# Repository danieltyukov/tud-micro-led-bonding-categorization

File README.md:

# Micro-LED Bonding Categorization

**A PCB test vehicle, a cleanroom bonding campaign, and an electrical characterization of eight micro-LED assembly conditions.**

TU Delft ECTM + ITEC B.V., February to August 2026. Course project (ET4277 + ET4391) and research contribution, supervised by M. Mastrangeli, H. van Zeijl and A. Abdelwahab, with R. van Hoorn and H. Kuipers (ITEC B.V. / Nexperia). Financed by ITEC B.V. and co-financed by RVO. Extends the v1 board published at [ECTC 2025](https://doi.org/10.1109/ECTC51687.2025.00363).

The question behind the work: when a ~1 mm² LED die is attached to a PCB without mounting pressure (pick-and-release / air-drop), how good is the resulting bond, and what instrument does it take to tell one bonding process from another?

---

## Headline result

**Yield and failure mode separate the eight assembly conditions. Series resistance cannot, and the reason is measured rather than assumed.**

| Condition | Channel yield | Failure modes | Assessment |
|---|---:|---|---|
| 1 | 83.3 % | 1 open, 3 detached | under-bonded |
| 2 | 58.3 % | 4 open, 6 detached | under-bonded |
| 3 | 25.0 % | 4 short, 2 open, 2 cross-lit, 1 suspect | over-bonded, 1 shunt confirmed |
| 4 | 66.7 % | 1 short, 1 open, 1 cross-lit, 1 suspect | over-bonded |
| 5 | **100 %** | none | in window |
| 6 | 75.0 % | 3 detached | under-bonded |
| 7 | **100 %** | none | in window |
| 8 | 83.3 % | 2 short | over-bonded, survivors clean |

A χ² test on the yield and failure-mode distribution gives p = 2.2 × 10⁻⁴. Conditions 5 and 7 lost nothing across every channel.

Series resistance does not discriminate: one-way ANOVA over the seven samples with n ≥ 3 gives F(6,21) = 1.96, not significant. Re-seating the same two jumpers on an unchanged channel moves R_s by **0.84 Ω**, which is 85 % of the apparent die-to-die spread, while the bond resistances being chased are **10 to 100 mΩ**. The experiment was never capable of resolving them, and the repeatability study is what proves it.

<table>
<tr>
<td width="50%"></td>
<td width="50%"></td>
</tr>
<tr>
<td>Yield and failure mode per condition, with Wilson intervals.</td>
<td>Defect map: every die position, every condition.</td>
</tr>
</table>

---

## The three parts of the work

### 1. Board design

A single 93 × 93 mm two-layer FR-4 board (ENIG, all pads gold) carrying every structure needed to characterize a bond on one substrate, so that one cleanroom session yields bond resistance, contact resistivity, sheet resistance and junction thermometry from the same hardware:

- **6 × 6 bond-pad design of experiments** at 3.5 mm pitch: three pad geometries (plain, four corner mini-pads, rounded + mini) crossed with three fillet radii (50 / 100 / 200 µm).
- **TLM ladders** at W = 0.25 / 0.5 / 1.0 mm with spacings 200 to 4000 µm, and **van der Pauw cloverleaves** at W = 1.0 / 0.5 / 0.25 / 0.15 mm.
- **26 Würth WL-SFCC 0404 RGB LEDs**: eight individually addressable, eighteen in 6- and 12-die daisy chains.
- **Four 0402 NTCs** for V_F-based junction thermometry, and an **LCR calibration set** (open / short / 100 Ω 0.1 %).
- Two 32-pin headers breaking every active net out to a breadboard.

Designed in KiCad 9, DRC-clean with full schematic parity, exported fab-ready to the Eurocircuits standard pool. The five SMT parts are reflowed by the fab; the 26 LED bond pads ship as bare gold, because the joint itself is the research subject and has to form under controlled conditions.

Sources, Python generators and the full fab package (gerbers, BOM, CPL, STEP, PDFs) are in [`new-pcb/`](new-pcb/). Report: [`part1/`](part1/ET4277_ET4391_DanielTyukov_5714699_part1_microLED_PCB_electrical_characterization.pdf).

### 2. Cleanroom bonding

Solder paste printed by hand through a 100 µm stencil, dies placed with a Tresky T-3000-PRO die bonder, joint formed on a hot plate with Sn42/Bi57.6/Ag0.4 (T_melt = 138 °C). When the paste melts, surface tension pulls each die toward the centre of its pad set. The same forces can tilt a die and lock it in a crooked position that never recovers, because tilt is the one non-restoring self-alignment mode for a rectangular chip.

<table>
<tr>
<td width="50%"></td>
<td width="50%"></td>
</tr>
<tr>
<td>Board fixtured in the Tresky T-3000-PRO.</td>
<td>Printed bond-pad array before placement.</td>
</tr>
</table>

The analytical contribution is reading the observed self-alignment and tilt against the capillary self-alignment literature to identify which process variable dominates. It is **solder volume**: manual stencil printing gives no volume metering, and volume is exactly the quantity the literature ties most strongly to both placement accuracy and the non-restoring tilt mode.

Report: [`part2/`](part2/ET4277_ET4391_DanielTyukov_5714699_part2_microLED_bonding_self_alignment_die_tilt.pdf). Session photos in [`part2/photos-during-lab2/`](part2/photos-during-lab2/), references in [`part2/downloaded_references/`](part2/downloaded_references/).

### 3. Electrical characterization

Eight blind-coded assembly conditions across five coupons, 40 dice bonded, 4 detached in handling, 36 measurable, 120 individual-die channels. Run as two rounds so that a cheap screen filtered the expensive one.

**Round 1, DMM screen.** Every channel screened for opens, shorts, cross-lighting and detachment with a handheld meter. It called six channels bad; the sweep rig later agreed on all six and disagreed on none in 89 sweeps.

**Round 2, current sweep.** An Arduino UNO rig switching a six-resistor bank (220 Ω to 10 kΩ) against a 100 Ω sense resistor, 63 current levels per sweep, fitting V = V₀ + n·V_T·ln(I) + I·R_s to each channel. 89 channel sweeps plus 9 re-seating repeatability runs.

<table>
<tr>
<td width="50%"></td>
<td width="50%"></td>
</tr>
<tr>
<td>Red, green and blue junctions of one die.</td>
<td>The defect only a current sweep could see.</td>
</tr>
</table>

Three findings about the measurement itself carried more weight than the bond numbers:

- **The ideality factor is a free defect detector.** Any channel fitting outside n = 1.2 to 2.4 has something in parallel with the junction, however normal its curve looks at working current. It caught a ~2.9 kΩ shunt on a contaminated die that the DMM passed at 1.781 V.
- **Green and blue are not fittable at 5 V.** With V_F near 2.8 V the rail leaves only a 20× current range, so V₀, n and R_s trade off and green fits at an unphysical n = 3.2 to 4.0. Red gets 30× and fits cleanly at n = 1.60 to 2.06. Red only.
- **Four instrument defects were found and fixed mid-campaign**, including a hardcoded oversampling shift that would have rescaled every voltage, a 14.4 mV common ADC offset worth 26 % current error at the bottom of the sweep, and an integer-truncated bandgap reference putting a 2 to 3 mV floor on every reading.

Full working log with per-channel results: [`RESULTS/R2_REPORT.md`](RESULTS/R2_REPORT.md). Packaged deliverable with figures, MATLAB and raw data: [`deliverable/`](deliverable/microLED_electrical_characterization/).

**Dummy-die daisy chains (separate experiment, v1 board).** Measured by A. Abdelwahab on the v1 PCB in its own session, six Au-coated 1 mm² dummy dies per chain, one chain per condition. It resolves bond resistance where the LED coupons could not: 0.22 Ω on condition 5 against 0.61 Ω on condition 4, roughly 30 mΩ per joint, with a reported deviation of 11 to 20 mΩ. Its ranking agrees with the LED yield ranking at ρ = −0.92 (p = 0.003). That is agreement between assembly conditions across two different test vehicles and two campaigns, not two structures on one coupon, and it assumes the condition numbering matches. The v2 board carries daisy chains as well, but none were measured: a layout fault left them dead, so they were diagnosed and excluded rather than characterized (see Known limits). Data and figure: [`RESULTS/daisy_chain/`](RESULTS/daisy_chain/).

---

## Known limits

Stated up front, because they decide what these numbers can be used for.

| Limit | Consequence |
|---|---|
| Both voltage taps sit on the breadboard, not on the Tier-1 probe pads | Two female-male jumpers fall inside the measured loop. R_s is not usable for comparing bonds in this build. Kelvin sensing at the probe pads fixes it. |
| 5 V supply | Green and blue fits are unphysical. Red only. |
| Reverse bias measured through the meter's own 10 MΩ input impedance | Detects shunts below ~10 MΩ, cannot grade healthy dies. It confirmed the yield ranking rather than adding to it. |
| Daisy chains read open on every coupon | Layout fault, not a bonding failure: the dice sit rotated 90°, so the chain joins each die's red cathode to its blue cathode and leaves the anode floating. Fixed in the next revision. |
| One coupon carries uncleanable solder smear | Its readings characterize a post-process contamination failure and are excluded from V_F statistics. |
| No NTC readings collected | Ambient drift cannot be separated from self-heating at analysis time. |
| TLM, van der Pauw and impedance spectroscopy | Designed into the board, but the instruments were not available during the campaign. The structures are there for whoever has them. |

---

## Repository layout

| Path | Contents |
|---|---|
| [`new-pcb/`](new-pcb/) | v4 KiCad project, Python generators, Eurocircuits fab package, design notes |
| [`part1/`](part1/) | Board design and characterization-methodology report, project archive, fab quote |
| [`part2/`](part2/) | Bonding process report, cleanroom photos, self-alignment literature |
| [`FINAL_MEASUREMENTS/`](FINAL_MEASUREMENTS/) | Bench procedures, Arduino rig build drawings, MATLAB analysis, figures |
| [`RESULTS/`](RESULTS/) | Raw round 1 and round 2 data, per-channel results, round 2 report |
| [`measurements/`](measurements/) | Measurement plan, equipment limits, sample inventory, decision log |
| [`deliverable/`](deliverable/) | Self-contained characterization package: report, figures, code, data |
| [`old-pcb/`](old-pcb/) | v1 board (ECTC 2025), kept for reference |
| [`docs/`](docs/) | Datasheets, published papers, patent, collaboration notes |
| [`PROJECT_DETAILS.md`](PROJECT_DETAILS.md) | Full project context, v1 board teardown, literature notes |

## Reproducing the analysis

```
cd deliverable/microLED_electrical_characterization/matlab
matlab -batch figures
```

Reads `../data/`, refits every sweep, writes all eight figures, and prints every number quoted in the report. MATLAB R2025b with the Statistics and Machine Learning Toolbox (`anova1`, `chi2cdf`).

Board previews and fab outputs regenerate from `new-pcb/tools/`; see [`new-pcb/README.md`](new-pcb/README.md) and [`new-pcb/FABRICATION_ORDER.md`](new-pcb/FABRICATION_ORDER.md) for the ordering workflow.

## Reports

| Report | File |
|---|---|
| Part 1: A PCB Test Board for Electrical Characterization of Solder-Bonded Micro-LEDs | [PDF](part1/ET4277_ET4391_DanielTyukov_5714699_part1_microLED_PCB_electrical_characterization.pdf) |
| Part 2: Solder-Paste Printing and Die-Bonder Placement of Micro-LEDs, Capillary Self-Alignment and Die Tilt | [PDF](part2/ET4277_ET4391_DanielTyukov_5714699_part2_microLED_bonding_self_alignment_die_tilt.pdf) |
| Electrical characterization section (group deliverable) | [PDF](deliverable/Electrical_Characterization_section.pdf) |

## Tooling

KiCad 9, Python (fab, BOM and drawing generators), MATLAB R2025b, Arduino UNO / ATmega328P firmware, Eurocircuits PCB + PCBA, Tresky T-3000-PRO die bonder, eC-stencil-mate, handheld DMM.

## Credits

Daniel Tyukov (student no. 5714699), MSc Microelectronics, TU Delft. Supervision and cleanroom training: A. Abdelwahab, H. van Zeijl, M. Mastrangeli (TU Delft ECTM). Industrial partner: R. van Hoorn, H. Kuipers (ITEC B.V. / Nexperia). The v1 board and the pick-and-release method are the work of Abdelwahab et al., ECTC 2025, DOI [10.1109/ECTC51687.2025.00363](https://doi.org/10.1109/ECTC51687.2025.00363).

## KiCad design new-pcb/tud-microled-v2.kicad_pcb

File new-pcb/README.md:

# new-pcb — v2 Micro-LED Bonding Characterization PCB

**Status: fab-ready.** DRC clean (0 violations, 0 unconnected, 0 schematic-parity). Workflow: *Eurocircuits PCB + PCBA-proto*, all 3 BOM lines set to "Place on board" so the 4 NTC + 1 R + 2 header strips are reflowed / soldered by Eurocircuits. F.Paste has 10 apertures (NTC + R only); the 26 LED footprints stay paste-free and ship as bare ENIG gold for cleanroom bonding at TU Delft EKL.

## Quick links

- **Order from Eurocircuits** → `FABRICATION_ORDER.md`
- **As-built design notes** → `V2_DESIGN_NOTES.md`
- **Original spec** → `PCB_DESIGN_PLAN.md`
- **Electrical characterization workflow** → `ELECTRICAL_CHARACTERIZATION.md`
- **What this v2 contributes vs ECTC 2025** → `PUBLICATION_CONTRIBUTION.md`

## Folder layout

```
new-pcb/
├── tud-microled-v2.kicad_pro     KiCad 9.0.8 project
├── tud-microled-v2.kicad_pcb     PCB layout (130 footprints, DRC clean)
├── tud-microled-v2.kicad_sch     single-sheet A2 schematic
├── PCB_DESIGN_PLAN.md            original design spec
├── V2_DESIGN_NOTES.md            as-built notes
├── VERIFICATION_v4.md            electrical-characterization verification
├── ELECTRICAL_CHARACTERIZATION.md measurement plan + lab tools
├── FABRICATION_ORDER.md          Eurocircuits "Place loose" order checklist
├── PUBLICATION_CONTRIBUTION.md   v2 contributions vs ECTC 2025
├── library/                      Würth WL-SFCC LED symbol/footprint/3D
├── tools/                        Python helpers (PCB patcher, BOM generator)
└── fab/                          gerbers, BOM, pos, PDFs, STEP, top.png
    ├── tud-microled-v2-fab-bom.csv          BOM with TDK + Yageo + Samtec MPNs (Mouser PNs included)
    ├── tud-microled-v2-fab-bom-assembly-only.csv  slim BOM (the 3 assembled rows only)
    ├── tud-microled-v2-pos.csv               7 placements
    ├── tud-microled-v2-top.pdf / -bot.pdf    visual review
    ├── tud-microled-v2-gerbers.zip           26-file gerber + drill bundle
    ├── tud-microled-v2.step                  3D model
    └── preview/top.png                       1600×1600 raytraced render
```

## Design summary

| | |
|---|---|
| Board | 93 × 93 mm, 2-layer FR-4, 1.55 mm |
| Finish | ENIG (Ni 4 µm / Au 0.075 µm) |
| Min track / clearance | 0.20 / 0.30 mm (Eurocircuits Class 4 minimum is 0.15 mm) |
| Min drill / annular ring | 0.30 / 0.15 mm |
| Footprints on board | **130** (1 R + 4 NTC + 2 multi-pin headers + 26 LEDs DNP) |
| Distinct components | **3** (Yageo R, TDK NTC, Samtec header) |
| Placements per board (assembled) | **7** (1 R + 4 NTC + 2 header strips) |
| LED bonding | 26 × Würth WL-SFCC RGB at customer cleanroom (Tresky T-3000-PRO) |
| Solder-paste apertures | **10** on F.Paste (4 NTC × 2 + 1 R × 2). B.Paste empty. 26 LED footprints intentionally paste-free. |

## Bill of materials

3 distinct part numbers — all stocked at Mouser EU (1-day NL delivery) and resolvable through Eurocircuits' supplier scanner:

| Ref(s) | Manufacturer | MPN | Mouser PN |
|---|---|---|---|
| R_EIS_LOAD | Yageo | RT0603BRB07100RL | 603-RT0603BRB07100RL |
| H_N + H_S | Samtec | TSW-140-07-G-S | 200-TSW14007GS |
| TH1..TH4 | TDK | NTCG104BH103HT1 | 810-NTCG104BH103HT1 |

## Quick start

1. Open `tud-microled-v2.kicad_pro` in KiCad 9.0 or newer.
2. Confirm `WE_3DMODEL_DIR` is set in **Preferences → Configure Paths** (see `library/README.md`).
3. Run checks: `kicad-cli pcb drc tud-microled-v2.kicad_pcb` and `kicad-cli sch erc tud-microled-v2.kicad_sch` — both should report 0 violations.
4. Regenerate fab outputs after any PCB edit:
   - `kicad-cli pcb export gerbers --output fab/gerbers/ tud-microled-v2.kicad_pcb`
   - `kicad-cli pcb export drill --output fab/gerbers/ tud-microled-v2.kicad_pcb`
   - `kicad-cli pcb export pos --format csv --units mm --use-drill-file-origin --output fab/tud-microled-v2-pos.csv tud-microled-v2.kicad_pcb`
   - `kicad-cli pcb export pdf --layers F.Cu,F.Silkscreen,F.Mask,Edge.Cuts -o fab/tud-microled-v2-top.pdf tud-microled-v2.kicad_pcb`
   - `kicad-cli pcb render --side top --width 1600 --height 1600 --quality high --output fab/preview/top.png tud-microled-v2.kicad_pcb`
   - `python3 tools/gen_fab_bom.py` to refresh the BOM CSV
   - `(cd fab/gerbers && zip -q ../tud-microled-v2-gerbers.zip *)` to rebundle for Eurocircuits

## tools/ scripts

| Script | Purpose |
|---|---|
| `gen_fab_bom.py` | Reads `fab/tud-microled-v2-pos.csv`, emits `tud-microled-v2-fab-bom.csv` + slim variant |
| `patch_aisler_mpns.py` | Adds Manufacturer + MPN custom fields to each footprint so any fab auto-detects them |
| `consolidate_pcb.py` | One-time refactor that collapsed 64 single-pin headers into 2 multi-pin strips and deleted the 123 bare-pad design-only footprints |
| `strip_all_paste.py` | Removes F.Paste / B.Paste from every pad in the design (used for the loose-components workflow) |
| `clean_dangling.py` | Removes orphan tracks/vias left over by `consolidate_pcb.py` |
| `unify_values.py` | Sets the `Value` field of every footprint to its MPN so Aisler/EC Grouped views collapse them properly |
| `inspect_headers.py` | Read-only debug helper |

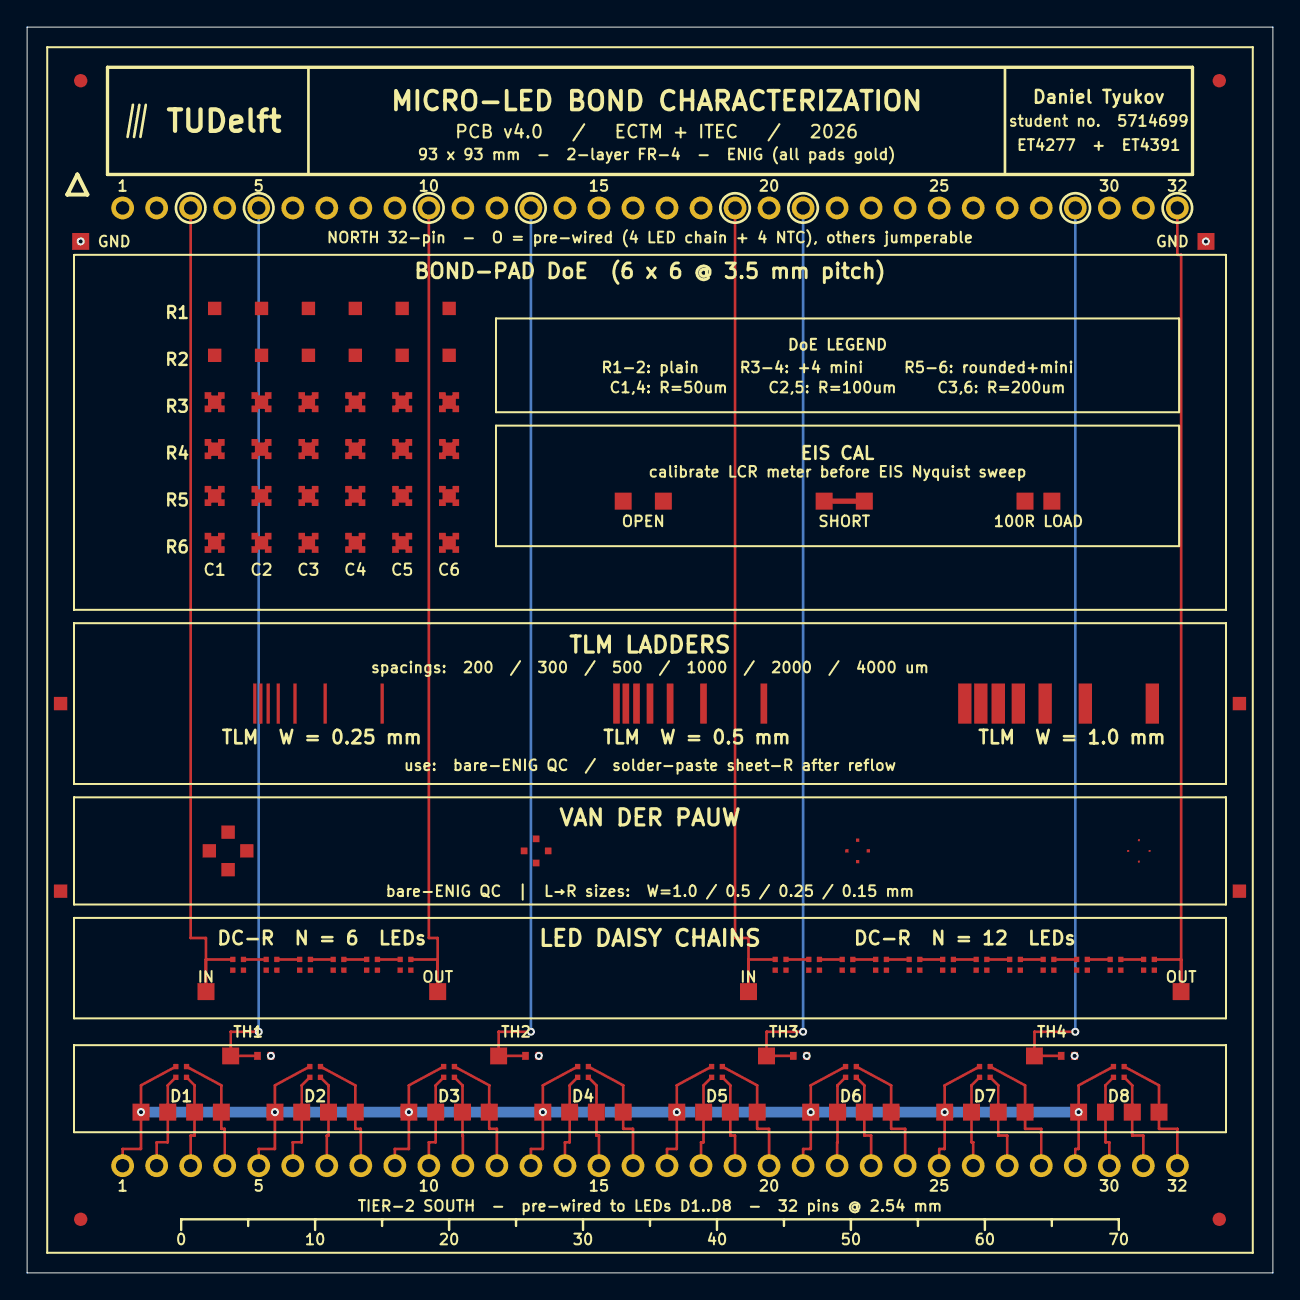
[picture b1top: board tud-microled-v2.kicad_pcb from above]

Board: 2 copper layers, 93.0 x 93.0 mm, 130 parts (0 on the bottom side), 51 nets.

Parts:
BP_R1C1: BP_R1C1; BondPad_DoE
BP_R1C2: BP_R1C2; BondPad_DoE
BP_R1C3: BP_R1C3; BondPad_DoE
BP_R1C4: BP_R1C4; BondPad_DoE
BP_R1C5: BP_R1C5; BondPad_DoE
BP_R1C6: BP_R1C6; BondPad_DoE
BP_R2C1: BP_R2C1; BondPad_DoE
BP_R2C2: BP_R2C2; BondPad_DoE
BP_R2C3: BP_R2C3; BondPad_DoE
BP_R2C4: BP_R2C4; BondPad_DoE
BP_R2C5: BP_R2C5; BondPad_DoE
BP_R2C6: BP_R2C6; BondPad_DoE
BP_R3C1: BP_R3C1; BondPad_DoE
BP_R3C2: BP_R3C2; BondPad_DoE
BP_R3C3: BP_R3C3; BondPad_DoE
BP_R3C4: BP_R3C4; BondPad_DoE
BP_R3C5: BP_R3C5; BondPad_DoE
BP_R3C6: BP_R3C6; BondPad_DoE
BP_R4C1: BP_R4C1; BondPad_DoE
BP_R4C2: BP_R4C2; BondPad_DoE
BP_R4C3: BP_R4C3; BondPad_DoE
BP_R4C4: BP_R4C4; BondPad_DoE
BP_R4C5: BP_R4C5; BondPad_DoE
BP_R4C6: BP_R4C6; BondPad_DoE
BP_R5C1: BP_R5C1; BondPad_DoE
BP_R5C2: BP_R5C2; BondPad_DoE
BP_R5C3: BP_R5C3; BondPad_DoE
BP_R5C4: BP_R5C4; BondPad_DoE
BP_R5C5: BP_R5C5; BondPad_DoE
BP_R5C6: BP_R5C6; BondPad_DoE
BP_R6C1: BP_R6C1; BondPad_DoE
BP_R6C2: BP_R6C2; BondPad_DoE
BP_R6C3: BP_R6C3; BondPad_DoE
BP_R6C4: BP_R6C4; BondPad_DoE
BP_R6C5: BP_R6C5; BondPad_DoE
BP_R6C6: BP_R6C6; BondPad_DoE
D1, D2, D3, D4, D5, D6, D7, D8: WL-SFCC RGB (DNP); WL-SFCC_0404
DCL6_L1, DCL6_L2, DCL6_L3, DCL6_L4, DCL6_L5, DCL6_L6, DCL12_L1, DCL12_L2, DCL12_L3, DCL12_L4, DCL12_L5, DCL12_L6, DCL12_L7, DCL12_L8, DCL12_L9, DCL12_L10, DCL12_L11, DCL12_L12: WL-SFCC RGB (DNP); WL-SFCC_0404
FID1: FID1; Fiducial_1mm
FID2: FID2; Fiducial_1mm
FID3: FID3; Fiducial_1mm
FID4: FID4; Fiducial_1mm
H_N: TSW-140-07-G-S; Header_2.54mm
H_S: TSW-140-07-G-S; Header_2.54mm
PP_D1_A: PP_D1_A; Probe_1.27mm
PP_D1_KB: PP_D1_KB; Probe_1.27mm
PP_D1_KG: PP_D1_KG; Probe_1.27mm
PP_D1_KR: PP_D1_KR; Probe_1.27mm
PP_D2_A: PP_D2_A; Probe_1.27mm
PP_D2_KB: PP_D2_KB; Probe_1.27mm
PP_D2_KG: PP_D2_KG; Probe_1.27mm
PP_D2_KR: PP_D2_KR; Probe_1.27mm
PP_D3_A: PP_D3_A; Probe_1.27mm
PP_D3_KB: PP_D3_KB; Probe_1.27mm
PP_D3_KG: PP_D3_KG; Probe_1.27mm
PP_D3_KR: PP_D3_KR; Probe_1.27mm
PP_D4_A: PP_D4_A; Probe_1.27mm
PP_D4_KB: PP_D4_KB; Probe_1.27mm
PP_D4_KG: PP_D4_KG; Probe_1.27mm
PP_D4_KR: PP_D4_KR; Probe_1.27mm
PP_D5_A: PP_D5_A; Probe_1.27mm
PP_D5_KB: PP_D5_KB; Probe_1.27mm
PP_D5_KG: PP_D5_KG; Probe_1.27mm
PP_D5_KR: PP_D5_KR; Probe_1.27mm
PP_D6_A: PP_D6_A; Probe_1.27mm
PP_D6_KB: PP_D6_KB; Probe_1.27mm
PP_D6_KG: PP_D6_KG; Probe_1.27mm
PP_D6_KR: PP_D6_KR; Probe_1.27mm
PP_D7_A: PP_D7_A; Probe_1.27mm
PP_D7_KB: PP_D7_KB; Probe_1.27mm
PP_D7_KG: PP_D7_KG; Probe_1.27mm
PP_D7_KR: PP_D7_KR; Probe_1.27mm
PP_D8_A: PP_D8_A; Probe_1.27mm
PP_D8_KB: PP_D8_KB; Probe_1.27mm
PP_D8_KG: PP_D8_KG; Probe_1.27mm
PP_D8_KR: PP_D8_KR; Probe_1.27mm
PP_DCL6_IN: PP_DCL6_IN; Probe_1.27mm
PP_DCL6_OUT: PP_DCL6_OUT; Probe_1.27mm
PP_DCL12_IN: PP_DCL12_IN; Probe_1.27mm
PP_DCL12_OUT: PP_DCL12_OUT; Probe_1.27mm
PP_EIS_OPEN_A: PP_EIS_OPEN_A; Probe_1.27mm
PP_EIS_OPEN_B: PP_EIS_OPEN_B; Probe_1.27mm
PP_EIS_SHORT_A: PP_EIS_SHORT_A; Probe_1.27mm
PP_EIS_SHORT_B: PP_EIS_SHORT_B; Probe_1.27mm
PP_GND1: PP_GND1; Probe_1.27mm
PP_GND2: PP_GND2; Probe_1.27mm
PP_NTC1: PP_NTC1; Probe_1.27mm
PP_NTC2: PP_NTC2; Probe_1.27mm
PP_NTC3: PP_NTC3; Probe_1.27mm
PP_NTC4: PP_NTC4; Probe_1.27mm
R_EIS_LOAD: RT0603BRB07100RL; EIS_Load_0603
TC1: TC1; TC_Pad_1mm
TC2: TC2; TC_Pad_1mm
TC3: TC3; TC_Pad_1mm
TC4: TC4; TC_Pad_1mm
TH1, TH2, TH3, TH4: NTCG104BH103HT1; NTC_0402
TLM_W0.5: TLM_W0.5; TLM
TLM_W0.25: TLM_W0.25; TLM
TLM_W1.0: TLM_W1.0; TLM
VDP_W0.5: VDP_W0.5; VDP
VDP_W0.15: VDP_W0.15; VDP
VDP_W0.25: VDP_W0.25; VDP
VDP_W1.0: VDP_W1.0; VDP

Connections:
DCL6_IN: DCL6_L1.1, H_N.3, PP_DCL6_IN.1
DCL6_J1: DCL6_L1.2, DCL6_L2.1
DCL6_J2: DCL6_L2.2, DCL6_L3.1
DCL6_J3: DCL6_L3.2, DCL6_L4.1
DCL6_J4: DCL6_L4.2, DCL6_L5.1
DCL6_J5: DCL6_L5.2, DCL6_L6.1
DCL6_OUT: DCL6_L6.2, H_N.10, PP_DCL6_OUT.1
DCL12_IN: DCL12_L1.1, H_N.19, PP_DCL12_IN.1
DCL12_J1: DCL12_L1.2, DCL12_L2.1
DCL12_J2: DCL12_L2.2, DCL12_L3.1
DCL12_J3: DCL12_L3.2, DCL12_L4.1
DCL12_J4: DCL12_L4.2, DCL12_L5.1
DCL12_J5: DCL12_L5.2, DCL12_L6.1
DCL12_J6: DCL12_L6.2, DCL12_L7.1
DCL12_J7: DCL12_L7.2, DCL12_L8.1
DCL12_J8: DCL12_L8.2, DCL12_L9.1
DCL12_J9: DCL12_L9.2, DCL12_L10.1
DCL12_J10: DCL12_L10.2, DCL12_L11.1
DCL12_J11: DCL12_L11.2, DCL12_L12.1
DCL12_OUT: DCL12_L12.2, H_N.32, PP_DCL12_OUT.1
EIS_SHORT: PP_EIS_SHORT_A.1, PP_EIS_SHORT_B.1
GND: PP_GND1.1, PP_GND2.1, TH1.2, TH2.2, TH3.2, TH4.2
LED1_KB: D1.3, H_S.3, PP_D1_KB.1
LED1_KG: D1.4, H_S.2, PP_D1_KG.1
LED1_KR: D1.2, H_S.4, PP_D1_KR.1
LED2_KB: D2.3, H_S.7, PP_D2_KB.1
LED2_KG: D2.4, H_S.6, PP_D2_KG.1
LED2_KR: D2.2, H_S.8, PP_D2_KR.1
LED3_KB: D3.3, H_S.11, PP_D3_KB.1
LED3_KG: D3.4, H_S.10, PP_D3_KG.1
LED3_KR: D3.2, H_S.12, PP_D3_KR.1
LED4_KB: D4.3, H_S.15, PP_D4_KB.1
LED4_KG: D4.4, H_S.14, PP_D4_KG.1
LED4_KR: D4.2, H_S.16, PP_D4_KR.1
LED5_KB: D5.3, H_S.19, PP_D5_KB.1
LED5_KG: D5.4, H_S.18, PP_D5_KG.1
LED5_KR: D5.2, H_S.20, PP_D5_KR.1
LED6_KB: D6.3, H_S.23, PP_D6_KB.1
LED6_KG: D6.4, H_S.22, PP_D6_KG.1
LED6_KR: D6.2, H_S.24, PP_D6_KR.1
LED7_KB: D7.3, H_S.27, PP_D7_KB.1
LED7_KG: D7.4, H_S.26, PP_D7_KG.1
LED7_KR: D7.2, H_S.28, PP_D7_KR.1
LED8_KB: D8.3, H_S.31, PP_D8_KB.1
LED8_KG: D8.4, H_S.30, PP_D8_KG.1
LED8_KR: D8.2, H_S.32, PP_D8_KR.1
LED_VCC: D1.1, D2.1, D3.1, D4.1, D5.1, D6.1, D7.1, D8.1, H_S.1, H_S.5, H_S.9, H_S.13, H_S.17, H_S.21, H_S.25, H_S.29, PP_D1_A.1, PP_D2_A.1, PP_D3_A.1, PP_D4_A.1, PP_D5_A.1, PP_D6_A.1, PP_D7_A.1, PP_D8_A.1
NTC1: H_N.5, PP_NTC1.1, TH1.1
NTC2: H_N.13, PP_NTC2.1, TH2.1
NTC3: H_N.21, PP_NTC3.1, TH3.1
NTC4: H_N.29, PP_NTC4.1, TH4.1

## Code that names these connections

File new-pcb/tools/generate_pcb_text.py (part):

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    """Map a SOUTH-header pin index (1..32) to its assigned LED net.

    All 8 LEDs × 4 signals = 32 nets headerized into a 32-pin row.
    Pin 1  → D1 A  (LED_VCC)
    Pin 2  → D1 KG
    ...
    Pin 32 → D8 KR"""
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    # Top corners only — bottom strip is now taken by the mm ruler.
    # B.Cu GND pour still gives return-path access everywhere.
    # GND probe X positions chosen to clear the new 32-pin north header
    # (pin 1 at x=7.13, pin 32 at x=85.87) and the DCL12_OUT route at x=85.87.
    for i, (gx, gy) in enumerate([(4.0, 16.0), (BOARD_W - 5.0, 16.0)], 1):
        fps.append(probe_pad_footprint(f"PP_GND{i}", gx, gy, gnd))
        # Via to B.Cu GND pour
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    # then vertical down to the probe pad. All on F.Cu.
    chain_routes = [
        # (pin_idx, pin_x, target_x, target_y, route_y, label)
        ( 3, north_x0 +  2 * pin_pitch, 13.35, ROW_DAISY_PROBES, 68.0, "DCL6_IN"),
        (10, north_x0 +  9 * pin_pitch, 30.65, ROW_DAISY_PROBES, 68.0, "DCL6_OUT"),
        (19, north_x0 + 18 * pin_pitch, 53.85, ROW_DAISY_PROBES, 68.0, "DCL12_IN"),
        # Pin 32 has to detour: a straight vertical at pin 32's X (= 85.87 on
        # 93mm board) collides with VDP_W=0.1's right contact at (85.8, 61.5).
        # Route jogs right to x=86.15 just below the north header keepout,
        # then drops straight down to the chain probe.
        (32, north_x0 + 31 * pin_pitch, 86.15, ROW_DAISY_PROBES, None, "DCL12_OUT"),
    ]
    north_assignments = []
    for pin_idx, pin_x_val, tx, ty, jog_y, label in chain_routes:
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
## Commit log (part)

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2026-05-16 Initial commit: reorganize repo, vendor Würth WL-SFCC library, draft v2 plan
    - Move PDFs and the Ahmed work-plan note into docs/.
    - Move the existing 'Electrical test + LED-no solder' KiCad project into old-pcb/ (v1, ECTC-2025 paper).
    - Scaffold new-pcb/ for v2 design work.
    - Vendor official Würth Elektronik KiCad library for the WL-SFCC family
    (symbol, both 0404 footprints, both STEP 3D models) so the design is
    self-contained.
2026-05-16 Add electrical characterization plan (ports, lab tools, workflow)
    ELECTRICAL_CHARACTERIZATION.md covers:
    - Measurement strategy (Kelvin sensing, reference structures to isolate bond contribution from LED V_F)
    - What we can measure: V_F, I-V slope (R_s), daisy chain R, TLM rho_c, VDP R_sh, per-site bond R, leakage, lifetime drift, failure-mode signatures
    - 3-tier connector strategy: 1.27mm probe pads, 2.54mm headers, optional FFC edge connector
    - Lab tooling (day-one vs nice-to-have, TU Delft EKL equivalents)
    - End-to-end workflow diagram for cross-material comparison studies
2026-05-16 v2 PCB: fab-ready 100x80mm bond-characterization board
    DRC: 0 violations, 0 unconnected pads, 0 footprint errors.
    Generated procedurally by new-pcb/tools/generate_pcb_text.py (re-runnable).
    Footprints: 153 placed. Nets: 139.
    Structures (top → bottom):
    - 6x6 DoE bond-pad array (36 sites) with shape/radius/mini-pad sweep
    - 3 TLM ladders W=0.25/0.5/1.0mm, 6 contact spacings (5-200 µm)
2026-05-16 Include Gerber files in repo for fab handoff (zip stays ignored)
2026-05-16 Refactor PCB design settings and update electrical test configuration
    - Added a new user-edited backup file for the PCB design with comprehensive settings for design defaults, rules, and dimensions.
    - Updated the electrical test configuration by modifying the column widths to ensure proper alignment and sorting in the report.
2026-05-16 v3 PCB: 100x100mm board, full silkscreen polish, south header pre-wired
    Major changes vs prior v2:
    - Board grown 100x80 -> 100x100 mm (room for proper silkscreen)
    - Title block redesigned with 3 zones (TUDelft mark / project / student info)
    - Section frames around DoE, TLM, VDP, DC, LED rows
    - DoE LEGEND box on right with row/column descriptions
    - mm ruler at the bottom
2026-05-16 v3.5: add hardware for advanced LED electrical characterization
    NEW HARDWARE ADDITIONS (LED-characterization focused):
    - 4 x 0402 NTC thermistors (TH1-TH4) between LED pairs for V_F-TSP and
    aging temperature monitoring (Murata NCP15XH103 or compatible)
    - 4 x GND probe pads at corners with vias to B.Cu GND pour
    - 4 x 1mm gold TC pads (TC1-TC4) at TLM/VDP section edges for soldering
    fine-wire thermocouples during reflow profile measurement
2026-05-16 Refactor code structure for improved readability and maintainability
2026-05-16 Refactor PCB generation scripts and update layout parameters
    - Updated `gen_aisler_bom.py` to use CSV for reading component positions, improving readability and maintainability.
    - Adjusted lane Y positions in `generate_pcb_text.py` to ensure proper spacing and compliance with design rules.
    - Modified segment endpoints in `tud-microled-v2.kicad_pcb` to reflect updated lane positions, enhancing layout accuracy.
    - Updated binary PDF file for the PCB design to reflect the latest changes.
2026-05-16 Update pin header references and datasheets for improved accuracy
2026-05-16 Implement feature X to enhance user experience and fix bug Y in module Z
2026-05-16 Refresh docs + add schematic PNG to README
    - Root README.md: replace stale "not started" status table with current
    fab-ready state; embed board top/bottom renders + schematic PNG; add
    Aisler order quickstart.
    - new-pcb/README.md: full rewrite — folder layout now includes the
    generated PCB/schematic + fab outputs, design summary table, quickstart
    for KiCad workflow.
2026-05-16 Add IEEE conference template files and example content
    - Added IEEEtran_HOWTO.pdf for guidance on using the IEEEtran class.
    - Included conference_101719.pdf as a sample conference paper.
    - Created conference_101719.tex with structured content for a conference paper, including sections for title, authors, abstract, keywords, introduction, and references.
    - Added fig1.png as an example figure for the template.
2026-05-16 Add PCB test vehicle report files for electrical characterization of micro-LEDs
    - Created LaTeX document (report.tex) detailing the design, schematic, and measurement workflow of a 93mm x 93mm PCB test vehicle.
    - Included binary PDF output (report.pdf) generated from the LaTeX document.
    - Added bookmarks in the report output for easy navigation through sections.
2026-05-17 Refactor report content and update bookmarks
    - Revised the title and content of the report to better reflect the focus on the PCB test board for electrical characterization of solder-bonded Micro-LEDs.
    - Updated bookmarks in the report output to reflect changes in section titles and structure.
    - Adjusted the LaTeX document to improve clarity and conciseness, including rephrasing sections and enhancing descriptions of the board architecture and characterization methods.
    - Modified the schematic and net plan descriptions to align with the new board design and functionality.
    - Updated the tooling and assembly workflow to reflect the current processes and software used.
    - Enhanced the solder-pas
2026-05-17 Add new reference paper and update download links in references_to_download.md
    - Added "Polymer Reinforced Solder Paste for Improving Impact Energy Absorption Capability in Micro LED Laser-Assisted Mass Transfer" PDF to the references.
    - Updated the download links for all cited papers to clarify access via TU Delft proxy and indicate which references are bundled in the repository.
2026-05-17 Update report with new references and improve abstract clarity
2026-05-17 Add references for cited papers and include download links
    - Added a new PDF reference: "Polymer Reinforced Solder Paste for Improving Impact Energy Absorption Capability in Micro LED Laser-Assisted Mass Transfer."
    - Created a markdown file listing all cited papers with direct download links, including access notes for TU Delft resources.
2026-05-17 Remove outdated references and associated documents from the project repository
2026-05-17 Update PCB documentation and scripts for Eurocircuits compatibility
    - Enhanced README.md to reflect support for both Aisler and Eurocircuits, including updated ordering instructions and BOM generation.
    - Revised V2_DESIGN_NOTES.md to clarify compatibility with Eurocircuits Class-4 capabilities.
    - Updated VERIFICATION_v4.md to indicate copper thickness specifications for both Aisler and Eurocircuits.
    - Added new fab-neutral BOM generation script (gen_fab_bom.py) to accommodate both Aisler and Eurocircuits assembly processes.
    - Created new BOM file (tud-microled-v2-fab-bom.csv) for unified fabrication output.
    - Modified EMAIL.md to specify options for placing orders with either Aisler or Euroc
2026-05-17 Add order request email and KiCad project zip for micro-LED bonding PCB
2026-05-19 Refactor BOM files for Eurocircuits compatibility and add assembly-only BOM variant
2026-05-19 Remove email correspondence and related documents for ET4277/ET4391 project; update KiCad project zip file; fix BOM issues for Eurocircuits; switch to bare PCB order for faster turnaround.
2026-05-19 Update KiCad project files for microLED design; modified project archive to reflect recent changes.
2026-05-19 Finalize PCB for Eurocircuits order: - Updated Yageo resistor MPN from RT0603BRD07100RL to RT0603BRB07100RL for better availability and performance. - Added 3D model references for various footprints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
2026-05-20 Update Gerber files and PCB design for tud-microled-v2
    - Updated creation dates in Gerber files to 2026-05-20.
    - Added F.Paste layer to NTC_0402 and EIS_Load_0603 pads in the PCB design.
    - Restored F.Paste apertures for specific components in the SMT paste file.
    - Modified various user and eco files to reflect the new creation date.
    - Updated STEP file with new timestamp and minor directional adjustments.
    - Added a new script to automate the restoration of F.Paste for specific footprints.
2026-05-25 order
2026-05-25 Update report with new content and formatting changes
    - Updated the LaTeX document to include the eurosym package for Euro symbol support.
    - Revised component count and descriptions in the report for accuracy.
    - Adjusted references to specific components and their specifications.
    - Corrected line numbers in the log output for consistency.
    - Enhanced the PDF output with updated figures and improved formatting.
2026-05-26 Add report files for Part 2 of the micro-LED project
    - Create LaTeX source file for the report detailing the solder-paste printing and die-bonder placement of micro-LEDs.
    - Generate output PDF and bookmark file from the LaTeX source.
2026-05-26 Update report files and logs for Part 2 of the micro-LED project
2026-05-27 Add new component placement data to CPL file
2026-06-13 Add script to generate Electrical characterization section as a Word document
2026-06-20 Add corrected solder-paste stencil (F.Paste) for v2 board
    The first stencil had apertures on only 10 pads (TH1-4 + R_EIS_LOAD) because
    those were the sole pads carrying F.Paste, so it came back effectively
    "reversed" - open only where solder was already hand-applied.
    This rebuilds the F.Paste layer so the new mask snug-fits and prints paste
    where it's actually needed:
    - Add 1:1 paste apertures to all 327 exposed conductive pads (BondPad_DoE,
2026-06-20 Stencil v2: exclude probe/test/fiducial pads, widen header reliefs
    Per assembly intent, paste only goes on pads that get bonded/soldered:
    - Keep paste on DoE bond pads (BP_*), LED lands (D1-8, DCL6/DCL12), TC pads.
    - Remove paste from everything the probe station or vision touches: all PP_*
    probe pads (daisy-chain, per-LED, NTC, GND, EIS open/short cal), TLM/VDP
    test structures, and FID fiducials (87 pads -> bare copper, mask only).
    - Widen the H_N/H_S header reliefs (now 3.8 mm) so the already-soldered pins
2026-06-20 Stencil v2: keep solder on TLM ladders and Van der Pauw structures
    TLM/VDP are part of the solder/contact-resistance characterization, so they
    need paste after all. Re-added F.Paste to TLM_* and VDP_* (37 pads).
    Now 277 paste apertures. Still bare: PP_* probe pads + FID fiducials only.
    Noted that the 0.15/0.25 mm VDP squares are below reliable paste-release.
    DRC clean (0 violations).
    Claude-Session: https://claude.ai/code/session_011vFFhLhzgMnAtLoSZsN5RL
